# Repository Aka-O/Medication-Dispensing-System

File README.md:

# Medication-Dispensing-System
This project aims to create a product that will give users timely reminders to ingest their medication. It is aimed at patients who are taking short vacations or are away from home, and is equipped with various sensors to ensure the medication's integrity. A time module is included to give alerts when it's time to take medication.

Created for course ELEC3117 | Electrical Engineering Design

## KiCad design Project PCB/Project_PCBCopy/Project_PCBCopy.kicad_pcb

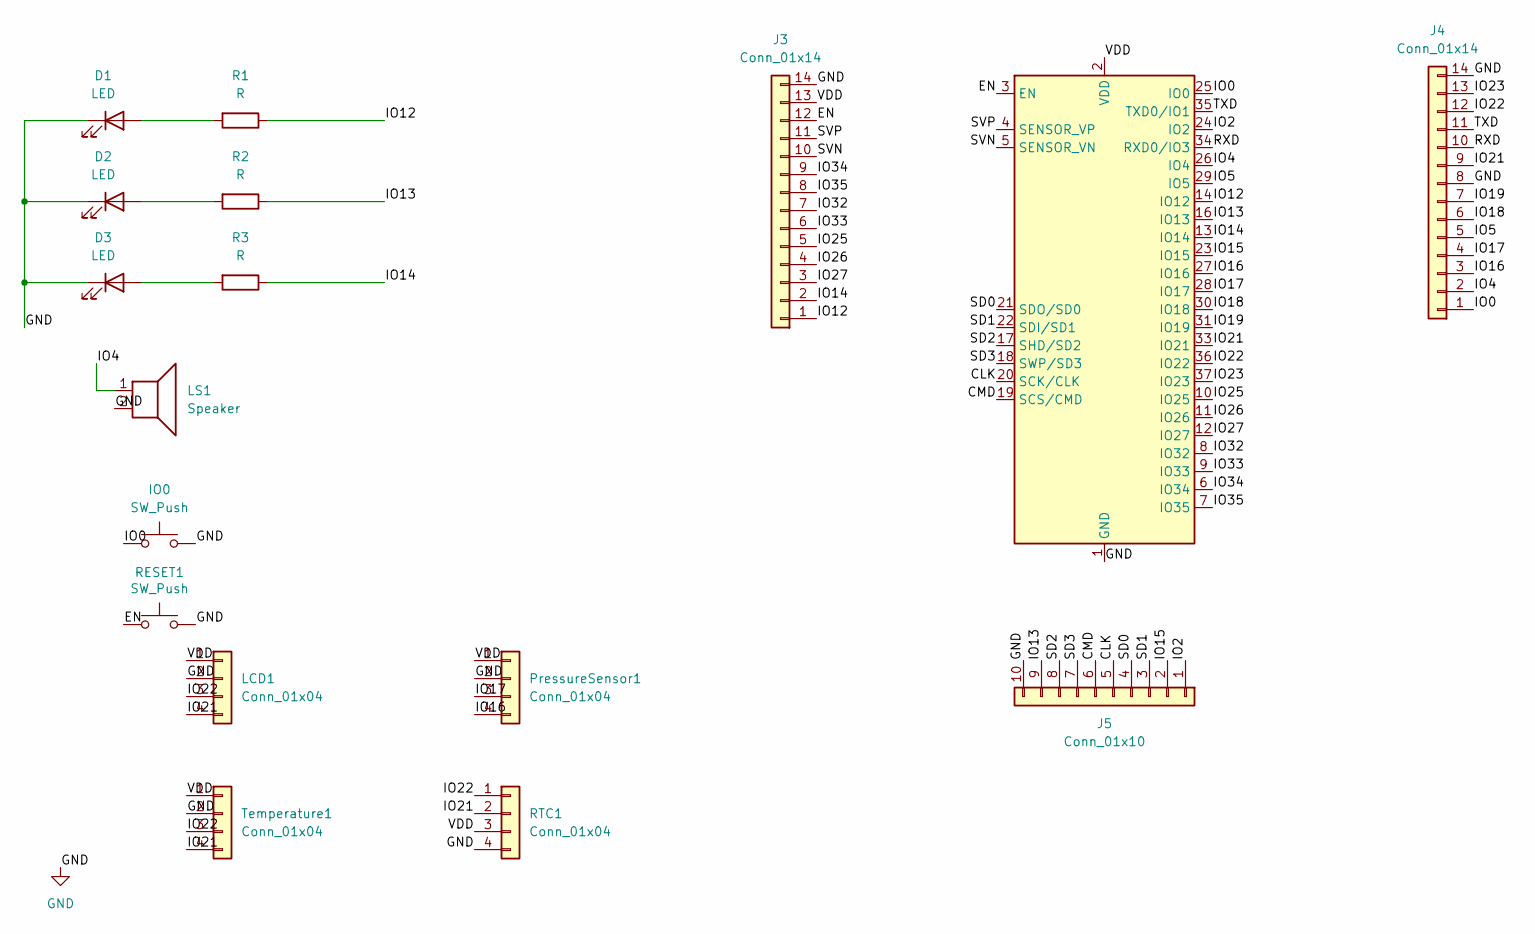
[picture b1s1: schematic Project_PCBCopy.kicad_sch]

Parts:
D1, D2, D3: LED; LED_D4.0mm
IO0: SW_Push; SW_PUSH_1P1T_6x3.5mm_H5.0_APEM_MJTP1250
J3, J4: Conn_01x14; PinHeader_1x14_P1.00mm_Vertical
J5: Conn_01x10; PinHeader_1x10_P1.00mm_Vertical
LCD1: Conn_01x04; PinHeader_1x04_P2.54mm_Vertical
LS1: Speaker; Buzzer_15x7.5RM7.6
PressureSensor1: Conn_01x04; PinHeader_1x04_P2.54mm_Vertical
R1, R2, R3: R; R_Axial_DIN0207_L6.3mm_D2.5mm_P7.62mm_Horizontal
RESET1: SW_Push; SW_PUSH_1P1T_6x3.5mm_H5.0_APEM_MJTP1250
RTC1: Conn_01x04; PinHeader_1x04_P2.54mm_Vertical
Temperature1: Conn_01x04; PinHeader_1x04_P2.54mm_Vertical
U1: ESP32-WROOM-32

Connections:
/CLK: J5.5, U1.20 (SCK/CLK)
/CMD: J5.6, U1.19 (SCS/CMD)
/EN: J3.12, RESET1.1, U1.3 (EN)
/IO0: IO0.1, J4.1, U1.25 (IO0)
/IO2: J5.1, U1.24 (IO2)
/IO4: J4.2, LS1.1, U1.26 (IO4)
/IO5: J4.5, U1.29 (IO5)
/IO12: J3.1, R1.1, U1.14 (IO12)
/IO13: J5.9, R2.1, U1.16 (IO13)
/IO14: J3.2, R3.1, U1.13 (IO14)
/IO15: J5.2, U1.23 (IO15)
/IO16: J4.3, PressureSensor1.4, U1.27 (IO16)
/IO17: J4.4, PressureSensor1.3, U1.28 (IO17)
/IO18: J4.6, U1.30 (IO18)
/IO19: J4.7, U1.31 (IO19)
/IO21: J4.9, LCD1.4, RTC1.2, Temperature1.4, U1.33 (IO21)
/IO22: J4.12, LCD1.3, RTC1.1, Temperature1.3, U1.36 (IO22)
/IO23: J4.13, U1.37 (IO23)
/IO25: J3.5, U1.10 (IO25)
/IO26: J3.4, U1.11 (IO26)
/IO27: J3.3, U1.12 (IO27)
/IO32: J3.7, U1.8 (IO32)
/IO33: J3.6, U1.9 (IO33)
/IO34: J3.9, U1.6 (IO34)
/IO35: J3.8, U1.7 (IO35)
/RXD: J4.10, U1.34 (RXD0/IO3)
/SD0: J5.4, U1.21 (SDO/SD0)
/SD1: J5.3, U1.22 (SDI/SD1)
/SD2: J5.8, U1.17 (SHD/SD2)
/SD3: J5.7, U1.18 (SWP/SD3)
/SVN: J3.10, U1.5 (SENSOR_VN)
/SVP: J3.11, U1.4 (SENSOR_VP)
/TXD: J4.11, U1.35 (TXD0/IO1)
/VDD: J3.13, LCD1.1, PressureSensor1.1, RTC1.3, Temperature1.1, U1.2 (VDD)
GND: D1.1 (K), D2.1 (K), D3.1 (K), IO0.2, J3.14, J4.8, J4.14, J5.10, LCD1.2, LS1.2, PressureSensor1.2, RESET1.2, RTC1.4, Temperature1.2, U1.1 (GND), U1.15 (GND), U1.38 (GND), U1.39 (GND)
unnamed: D1.2 (A), R1.2
unnamed: D2.2 (A), R2.2
unnamed: D3.2 (A), R3.2

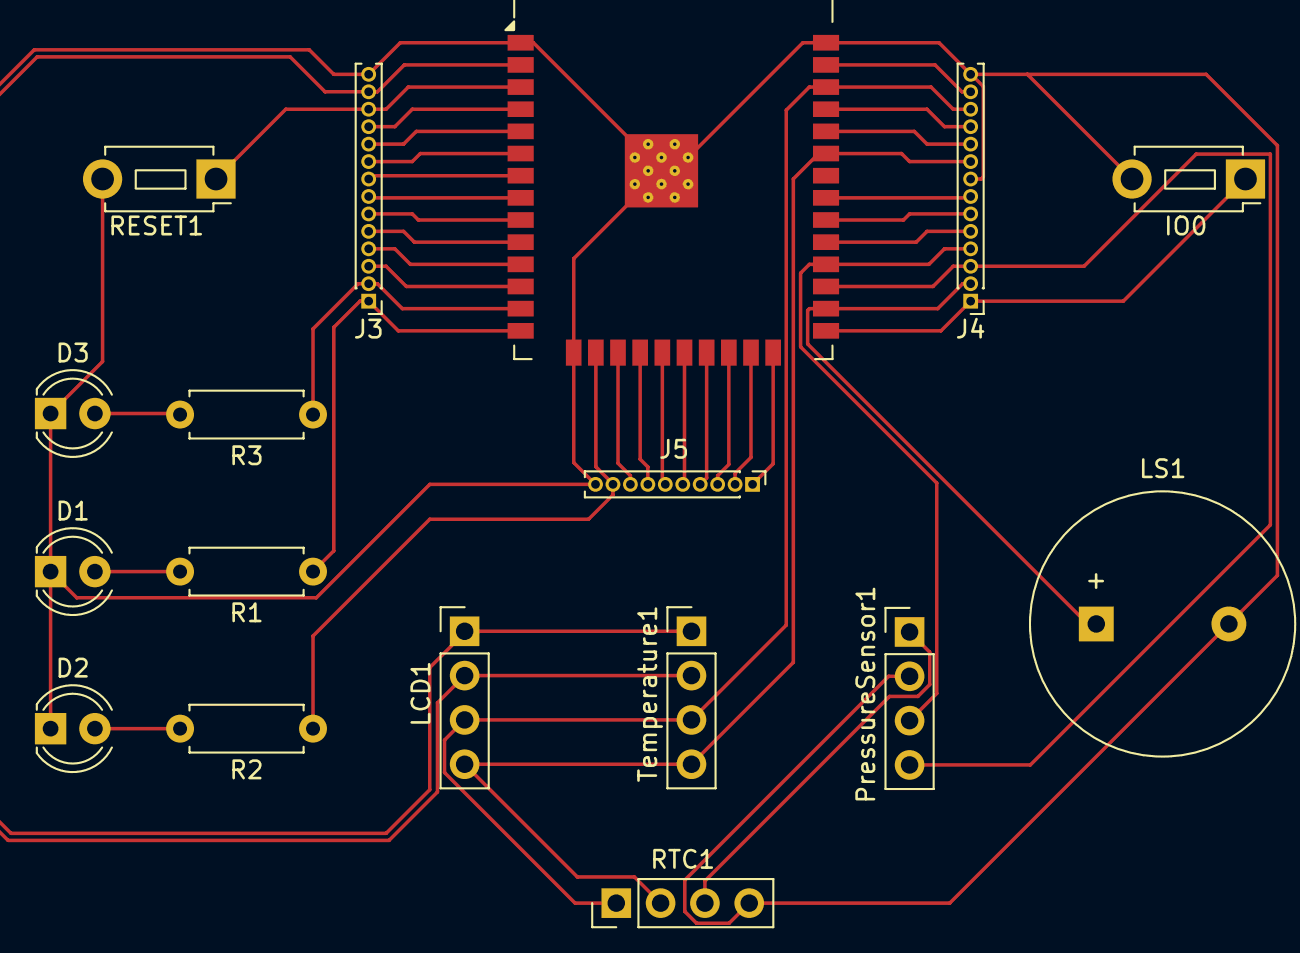
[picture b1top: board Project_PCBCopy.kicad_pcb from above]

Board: 2 copper layers, 17 parts (0 on the bottom side), 38 nets.

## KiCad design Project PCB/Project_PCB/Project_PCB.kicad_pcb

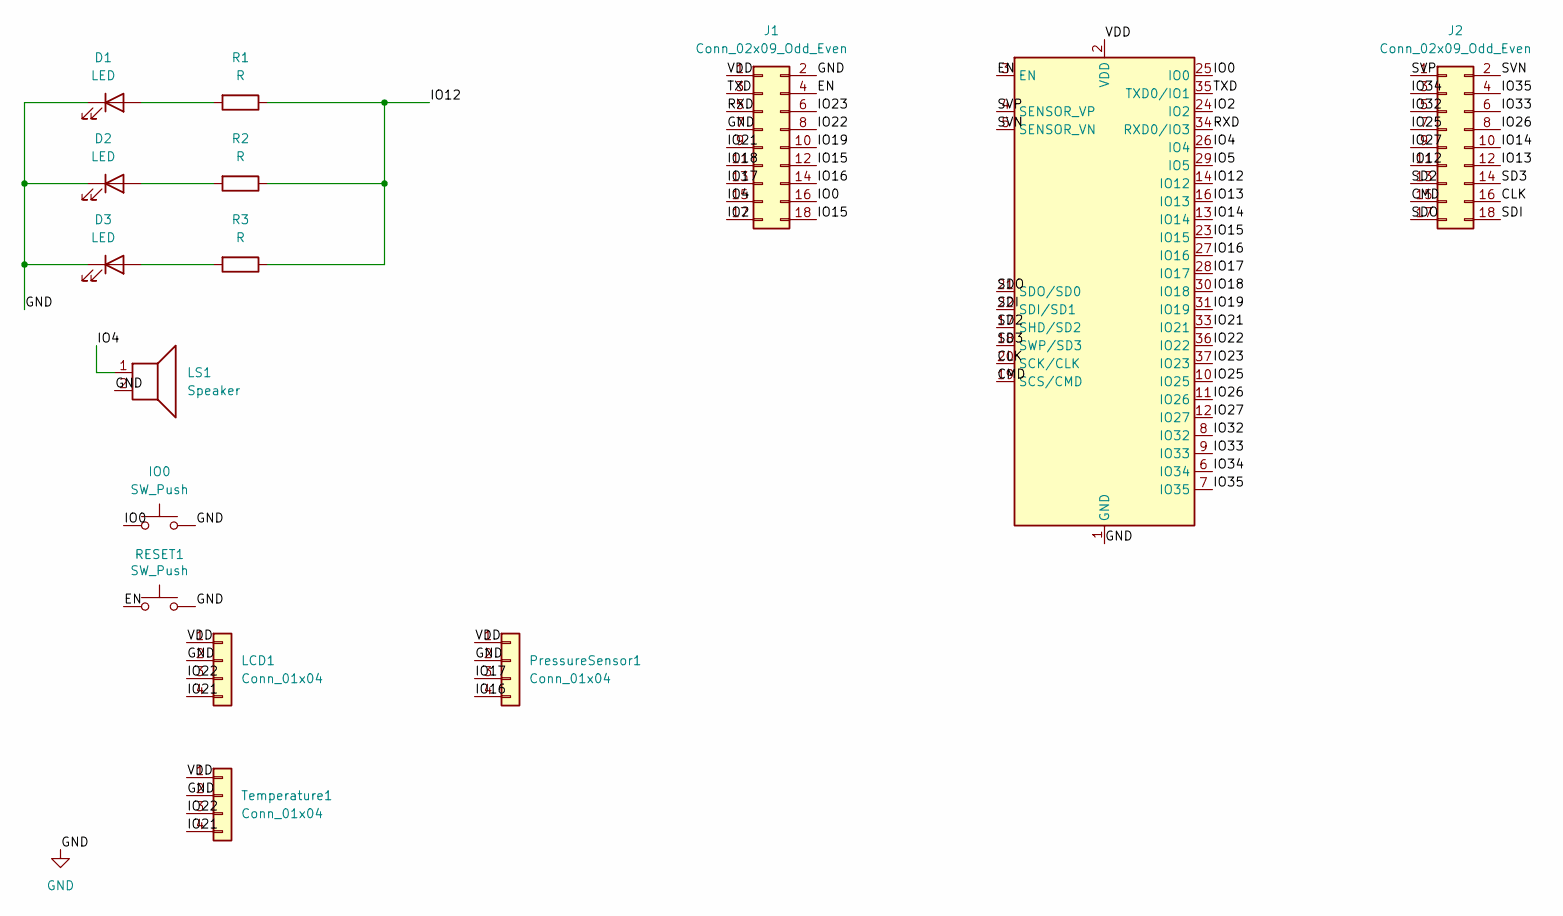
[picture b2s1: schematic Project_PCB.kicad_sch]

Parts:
D1, D2, D3: LED; LED_D4.0mm
IO0: SW_Push; SW_PUSH_1P1T_6x3.5mm_H5.0_APEM_MJTP1250
J1, J2: Conn_02x09_Odd_Even; PinHeader_2x09_P2.54mm_Vertical
LCD1: Conn_01x04; PinHeader_1x04_P2.54mm_Vertical
LS1: Speaker; Buzzer_15x7.5RM7.6
PressureSensor1: Conn_01x04; PinHeader_1x04_P2.54mm_Vertical
R1, R2, R3: R; R_Axial_DIN0207_L6.3mm_D2.5mm_P7.62mm_Horizontal
RESET1: SW_Push; SW_PUSH_1P1T_6x3.5mm_H5.0_APEM_MJTP1250
Temperature1: Conn_01x04; PinHeader_1x04_P2.54mm_Vertical
U1: ESP32-WROOM-32

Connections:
/CLK: J2.16, U1.20 (SCK/CLK)
/CMD: J2.15, U1.19 (SCS/CMD)
/EN: J1.4, RESET1.1, U1.3 (EN)
/IO0: IO0.1, J1.16, U1.25 (IO0)
/IO2: J1.17, U1.24 (IO2)
/IO4: J1.15, LS1.1, U1.26 (IO4)
/IO5: U1.29 (IO5)
/IO12: J2.11, R1.1, R2.1, R3.1, U1.14 (IO12)
/IO13: J2.12, U1.16 (IO13)
/IO14: J2.10, U1.13 (IO14)
/IO15: J1.12, J1.18, U1.23 (IO15)
/IO16: J1.14, PressureSensor1.4, U1.27 (IO16)
/IO17: J1.13, PressureSensor1.3, U1.28 (IO17)
/IO18: J1.11, U1.30 (IO18)
/IO19: J1.10, U1.31 (IO19)
/IO21: J1.9, LCD1.4, Temperature1.4, U1.33 (IO21)
/IO22: J1.8, LCD1.3, Temperature1.3, U1.36 (IO22)
/IO23: J1.6, U1.37 (IO23)
/IO25: J2.7, U1.10 (IO25)
/IO26: J2.8, U1.11 (IO26)
/IO27: J2.9, U1.12 (IO27)
/IO32: J2.5, U1.8 (IO32)
/IO33: J2.6, U1.9 (IO33)
/IO34: J2.3, U1.6 (IO34)
/IO35: J2.4, U1.7 (IO35)
/RXD: J1.5, U1.34 (RXD0/IO3)
/SD2: J2.13, U1.17 (SHD/SD2)
/SD3: J2.14, U1.18 (SWP/SD3)
/SDI: J2.18, U1.22 (SDI/SD1)
/SDO: J2.17, U1.21 (SDO/SD0)
/SVN: J2.2, U1.5 (SENSOR_VN)
/SVP: J2.1, U1.4 (SENSOR_VP)
/TXD: J1.3, U1.35 (TXD0/IO1)
/VDD: J1.1, LCD1.1, PressureSensor1.1, Temperature1.1, U1.2 (VDD)
GND: D1.1 (K), D2.1 (K), D3.1 (K), IO0.2, J1.2, J1.7, LCD1.2, LS1.2, PressureSensor1.2, RESET1.2, Temperature1.2, U1.1 (GND), U1.15 (GND), U1.38 (GND), U1.39 (GND)
unnamed: D1.2 (A), R1.2
unnamed: D2.2 (A), R2.2
unnamed: D3.2 (A), R3.2

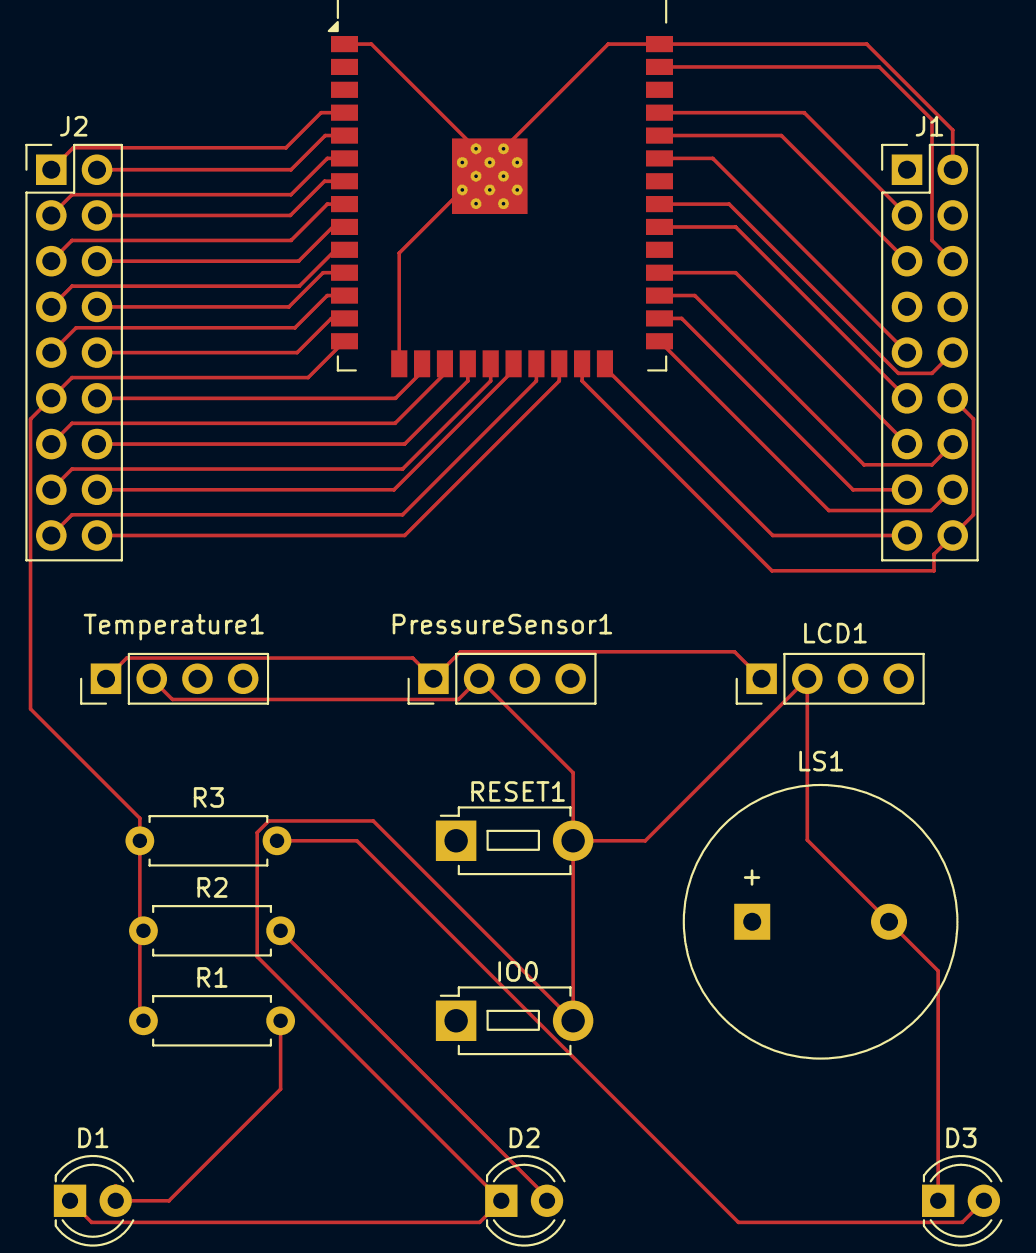
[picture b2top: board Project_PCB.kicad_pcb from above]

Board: 2 copper layers, 15 parts (0 on the bottom side), 37 nets.

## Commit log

2026-06-19 Create Power Supply PCB
